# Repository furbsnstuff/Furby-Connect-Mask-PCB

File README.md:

# Furby-Connect-Mask-PCB
!!!!!!!!.THIS IS STILL A WORK IN PROGRESS.!!!!!!!
# Furby Sleep Mask PCB

A replacement for the small "sleep mask" ID board that plugs into a Furby, so you can choose which personality it reads. Changing the resistor values changes the personality.

## How it works

The Furby identifies the mask by measuring a voltage, not by talking to a chip. The board is a small resistor network:

- The host pulls **J5-7** low, then **J5-8** low, and reads the voltage on **J5-4** each time.
- **R62** (100k) pulls J5-4 up to 3V3 and **C68** (100 nF) filters it.
- **R41** sets the J5-7 reading and **R42** sets the J5-8 reading.

Reading = 3.3 V × R / (R + 100k). For example, 18k gives about 0.50 V and 110k gives about 1.73 V. Fit different resistors to pick a different personality.

## Board

- 2 layers, about 28.6 × 23.04 mm (1.126 × 0.907 in)
- Eight round contact pads on the back (W1–W8), the Furby's only contact
- Eight through-hole wire pads (J5-3 to J5-8, VDD, GND)
- Parts: R41, R42, R62 (0805, 1%), C68 (100 nF, 0805)
- Suggested order options: ENIG finish, 1.6 mm thickness

## Files

| File | Contents |
|---|---|
| `mask.kicad_sch` | Schematic |
| `mask.kicad_pcb` | PCB layout |
| `mask_trimmer_sweep_log.xlsx` | Log sheet for sweeping a trimmer to find resistor values |

## Status

Work in progress and **untested**.

- The circuit is inferred from measurements of the original board, not from Furby firmware.
- Board size, pad positions and passive sizes came from photos of the original, so check them against a real mask before ordering.
- The J5-3, J5-5 and J5-6 pads are not used in this resistor-only version.
- The EEPROM option on the original board footprint is not included.

## Finding resistor values

1. Replace R42 (or R41) with a multi-turn trimmer.
2. Step through values and record the Furby's response in the sweep log.
3. Fit fixed 1% resistors once you know which values work.

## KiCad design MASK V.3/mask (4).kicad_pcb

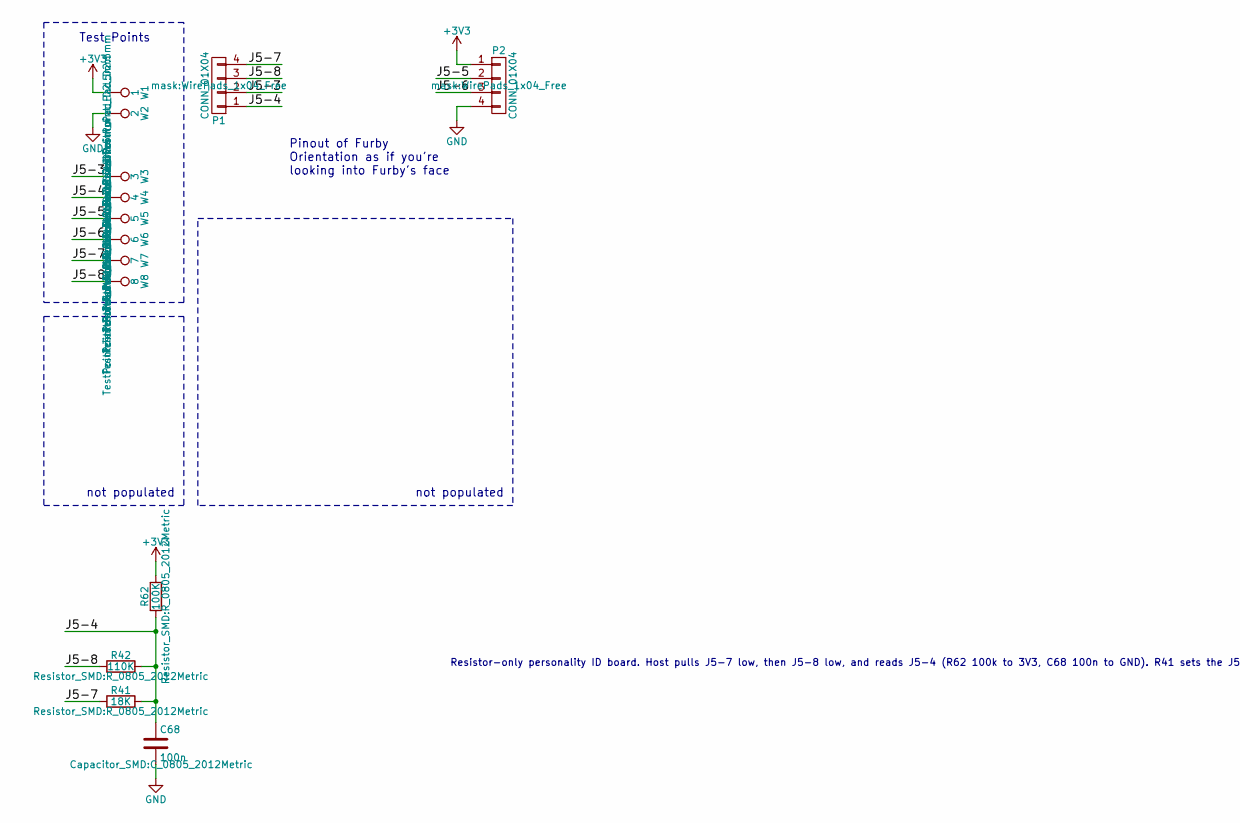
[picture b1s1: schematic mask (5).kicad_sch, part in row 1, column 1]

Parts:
C68: 100n; C_0805_2012Metric
P1, P2: CONN_01X04; WirePads_1x04_Free
R41: 18K; R_0805_2012Metric
R42: 110K; R_0805_2012Metric
R62: 100K; R_0805_2012Metric
W1: 1; TestPoint_Pad_D2.5mm
W2: 2; TestPoint_Pad_D2.5mm
W3: 3; TestPoint_Pad_D2.5mm
W4: 4; TestPoint_Pad_D2.5mm
W5: 5; TestPoint_Pad_D2.5mm
W6: 6; TestPoint_Pad_D2.5mm
W7: 7; TestPoint_Pad_D2.5mm
W8: 8; TestPoint_Pad_D2.5mm

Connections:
+3V3: P2.1, R62.2, W1.1; also elsewhere on the board
GND: C68.2, P2.4, W2.1
J5-3: P1.2, W3.1
J5-4: C68.1, P1.1, R41.2, R42.2, R62.1, W4.1
J5-5: P2.2, W5.1; also elsewhere on the board
J5-6: P2.3, W6.1
J5-7: P1.4, R41.1, W7.1
J5-8: P1.3, R42.1, W8.1

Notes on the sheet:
not populated
Pinout of Furby Orientation as if you're looking into Furby's face
Test Points
Resistor-only personality ID board. Host pulls J5-7 low, then J5-8 low, and reads J5-4 (R62 100k to 3V3, C68 100n to GND). R41 sets the J5-7 reading, R42 sets the J5-8 reading. J5-3, J5-5 and J5-6 are not used by this version. Footprints are assumed from photos, verify before ordering.

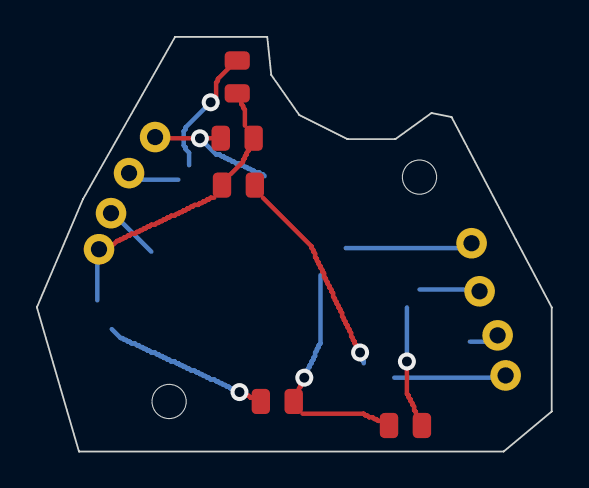
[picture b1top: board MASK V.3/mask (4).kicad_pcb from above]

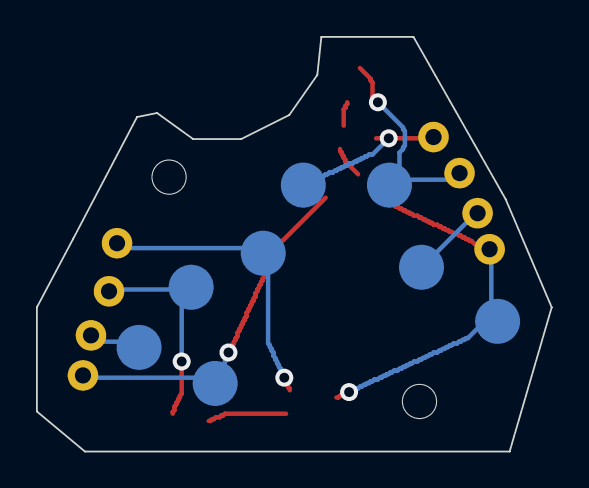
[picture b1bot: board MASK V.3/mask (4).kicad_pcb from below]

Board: 2 copper layers, 28.6 x 23.0 mm, 17 parts (8 on the bottom side), 8 nets.

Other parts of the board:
H1, H2: Hole; MountingHole_1.9mm
R59: 4K7; R_0805_2012Metric

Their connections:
+3V3: R59.1; also elsewhere on the board
J5-5: R59.2; also elsewhere on the board

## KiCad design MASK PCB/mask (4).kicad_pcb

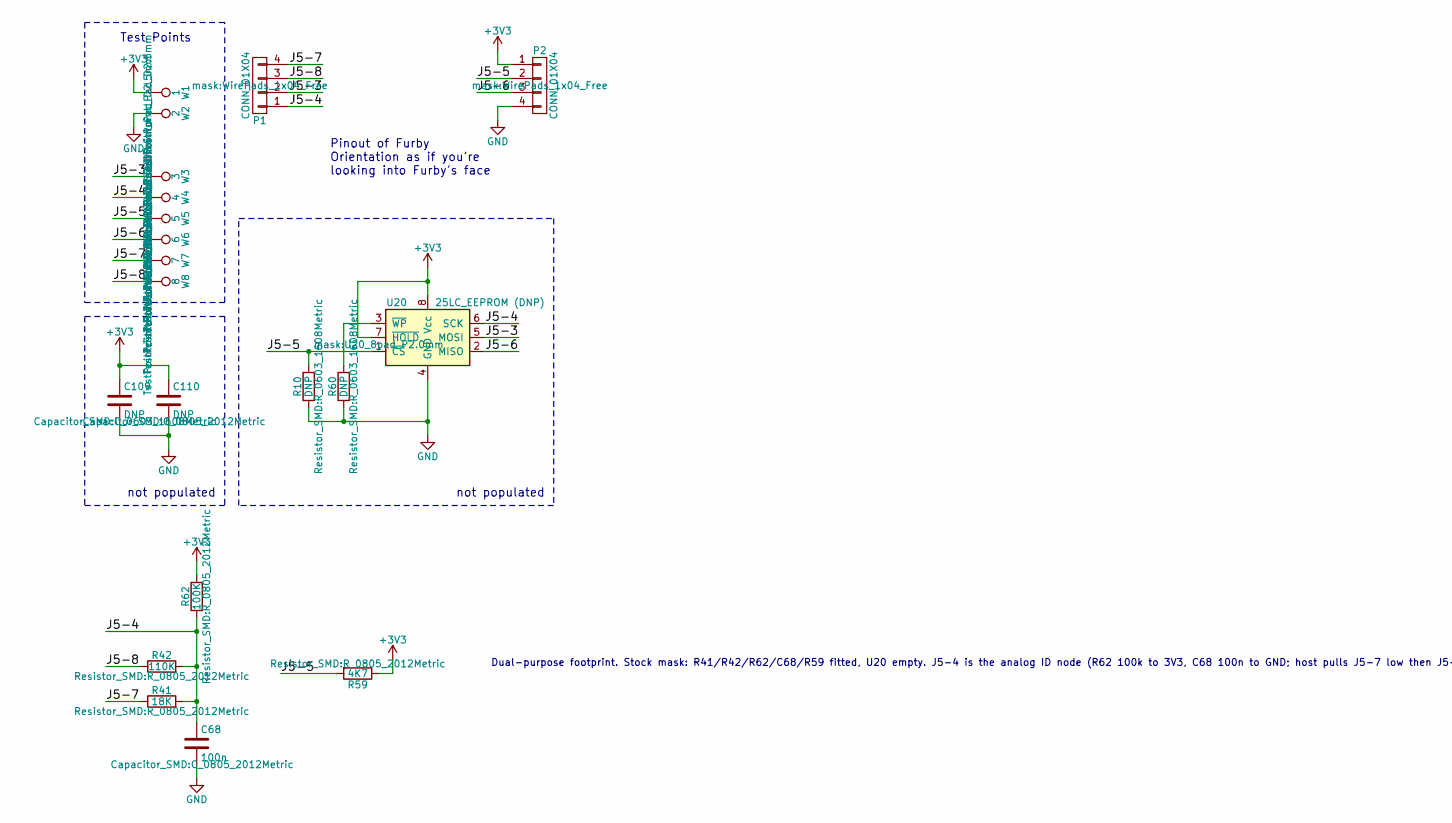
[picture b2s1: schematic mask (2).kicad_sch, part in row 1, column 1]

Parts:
C68: 100n; C_0805_2012Metric
C109: DNP; C_0603_1608Metric
C110: DNP; C_0805_2012Metric
P1, P2: CONN_01X04; WirePads_1x04_Free
R10, R60: DNP; R_0603_1608Metric
R41: 18K; R_0805_2012Metric
R42: 110K; R_0805_2012Metric
R59: 4K7; R_0805_2012Metric
R62: 100K; R_0805_2012Metric
U20: 25LC_EEPROM (DNP); U20_8pad_P2.0mm
W1: 1; TestPoint_Pad_D2.5mm
W2: 2; TestPoint_Pad_D2.5mm
W3: 3; TestPoint_Pad_D2.5mm
W4: 4; TestPoint_Pad_D2.5mm
W5: 5; TestPoint_Pad_D2.5mm
W6: 6; TestPoint_Pad_D2.5mm
W7: 7; TestPoint_Pad_D2.5mm
W8: 8; TestPoint_Pad_D2.5mm

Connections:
+3V3: C109.1, C110.1, P2.1, R59.1, R62.2, U20.7 (~HOLD), U20.8 (Vcc), W1.1
GND: C68.2, C109.2, C110.2, P2.4, R10.1, R60.1, U20.4 (GND), W2.1
J5-3: P1.2, U20.5 (MOSI), W3.1
J5-4: C68.1, P1.1, R41.2, R42.2, R62.1, U20.6 (SCK), W4.1
J5-5: P2.2, R10.2, R59.2, U20.1 (~CS), W5.1
J5-6: P2.3, U20.2 (MISO), W6.1
J5-7: P1.4, R41.1, W7.1
J5-8: P1.3, R42.1, W8.1
unnamed: R60.2, U20.3 (~WP)

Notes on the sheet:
not populated
Pinout of Furby Orientation as if you're looking into Furby's face
Test Points
Dual-purpose footprint. Stock mask: R41/R42/R62/C68/R59 fitted, U20 empty. J5-4 is the analog ID node (R62 100k to 3V3, C68 100n to GND; host pulls J5-7 low then J5-8 low). EEPROM variant: U20 = SPI 25LC, CS=J5-5, MISO=J5-6, MOSI=J5-3, SCK=J5-4. DNP: U20, R10, R60, C109, C110. Footprints are assume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

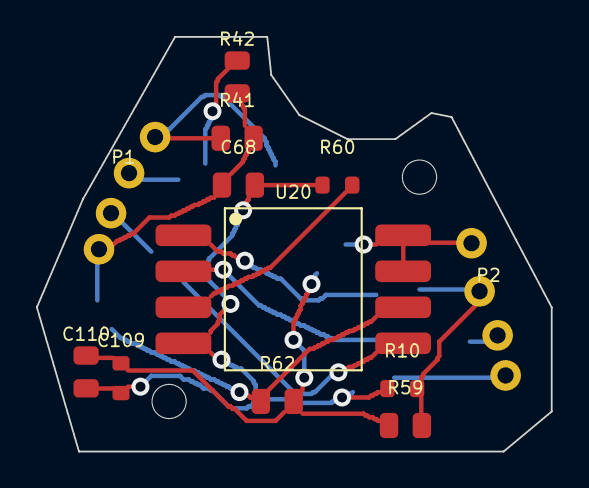
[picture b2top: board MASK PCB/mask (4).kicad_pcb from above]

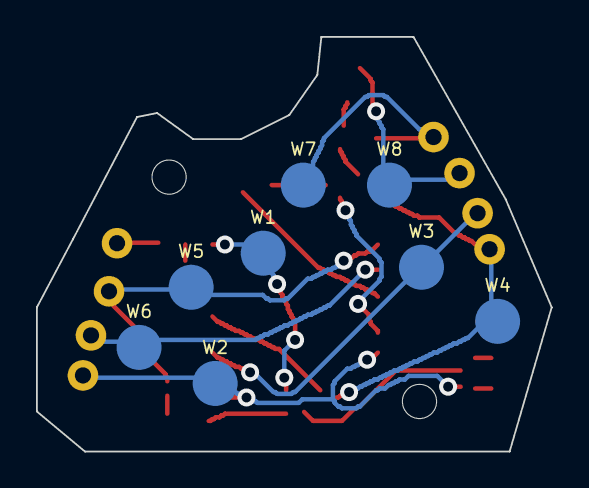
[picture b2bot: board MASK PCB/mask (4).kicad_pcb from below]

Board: 2 copper layers, 28.6 x 23.0 mm, 22 parts (8 on the bottom side), 9 nets.

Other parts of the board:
H1, H2: Hole; MountingHole_1.9mm
